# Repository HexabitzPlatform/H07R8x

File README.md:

# H07R8x-Hardware
Hexabitz 10W Stereo Audio Amplifier Module Hardware Design

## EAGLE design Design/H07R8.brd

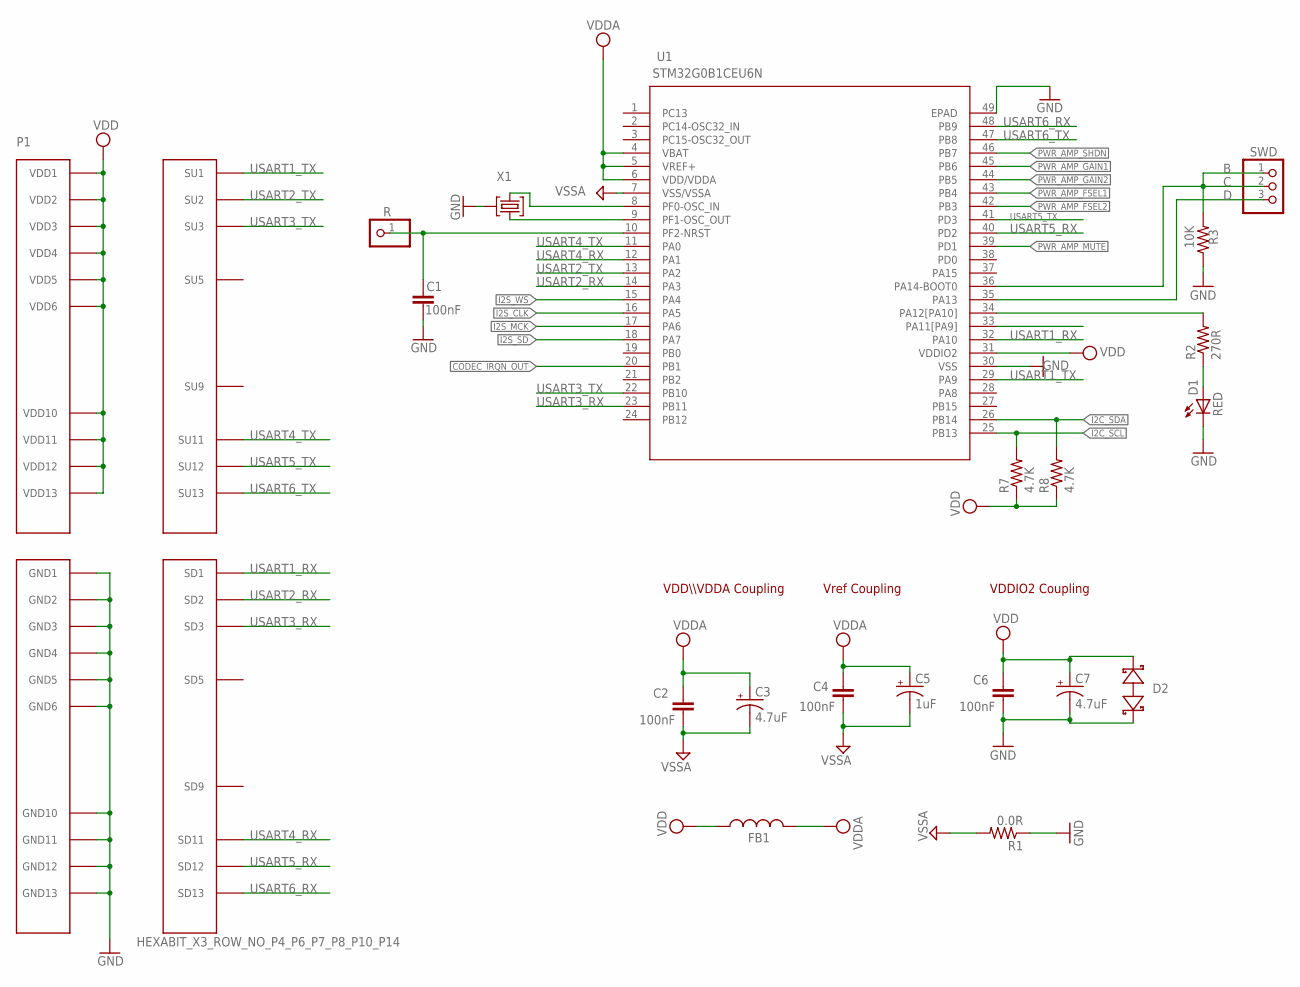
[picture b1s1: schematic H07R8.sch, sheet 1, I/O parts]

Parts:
C1: 100nF; C-0603; TOLERANCE 10%; VOLTAGE_RATING 16.0 V; MPN 0603YC104K4T2A
C2, C4, C6: 100nF; C-0603; TOLERANCE 10%; VOLTAGE_RATING 16.0 V; MPN '0603YC104K4T2A
C3: 4.7uF; C-0805-POL; TOLERANCE 20%; VOLTAGE_RATING 10.0 V; MPN '10TPU4R7MSI
C5: 1uF; C-0805-POL; TOLERANCE 20%; VOLTAGE_RATING 10.0 V; MPN 'CC0805KKX7R7BB105
C7: 4.7uF; C-0805-POL; TOLERANCE 10%; VOLTAGE_RATING 16.0 V; MPN '10TPU4R7MSI
D1: RED; VLMS1300-GS08
D2: BOURNS_CDSOD323-T03SCBOURNS_CDSOD323-T03SC_0_0; BOURNS_CDSOD323-T03SC_0
FB1: FB-TDK_MMZ1608Y300B; MPN MMZ1608Y300BTA00
P1: HEXABIT_X3_ROW_NO_P4_P6_P7_P8_P10_P14
R: PINHD-1X1; 1X01
R1: 0.0R; R-0603; MPN RC0603JR-070RL
R2: 270R; R-0603; MPN 'ERJ-3GEYJ271V
R3: 10K; R-0603; MPN '060300J0103T5E
R7, R8: 4.7K; R-0603; TOLERANCE ±1%; MPN RMCF0603FT4K70
SWD: PINHD-1X3; 1X03
TRIMBLE-LOGO3: HEXA-LOGO
U1: STM32G0B1CEU6N; HEXABITZ_ICS_QFN_B1CEU6_STM-L
X1: 8MHZ; XTALL_CSTCE8M00G52; MPN CSTNE8M00G550000R0

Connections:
C: R3.2, SWD.1, SWD.2, U1.36 (PA14-BOOT0)
CODEC_IRQN_OUT: U1.20 (PB1); also elsewhere on the board
D: SWD.3, U1.35 (PA13)
GND: C1.1, C6.1, C7.2 (-), D1.C, D2.1 (A), P1.PAD_PD15 (GND1), P1.PAD_PD16 (GND2), P1.PAD_PD17 (GND3), P1.PAD_PD18 (GND4), P1.PAD_PD19 (GND5), P1.PAD_PD24 (GND6), P1.PAD_PD25 (GND10), P1.PAD_PD26 (GND11), P1.PAD_PD27 (GND12), P1.PAD_PD28 (GND13), R1.1, R3.1, U1.30 (VSS), U1.49 (EPAD), X1.P$2 (2)
GND1: C2.1, C3.2 (-), C4.1, C5.2 (-), R1.2, U1.7 (VSS/VSSA); also elsewhere on the board
I2C_SCL: R7.2, U1.25 (PB13); also elsewhere on the board
I2C_SDA: R8.2, U1.26 (PB14); also elsewhere on the board
I2S_CLK: U1.16 (PA5); also elsewhere on the board
I2S_MCK: U1.17 (PA6); also elsewhere on the board
I2S_SD: U1.18 (PA7); also elsewhere on the board
I2S_WS: U1.15 (PA4); also elsewhere on the board
unnamed: U1.8 (PF0-OSC_IN), X1.P$1 (1)
unnamed: U1.9 (PF1-OSC_OUT), X1.P$3 (3)
unnamed: R2.2, U1.34 (PA12[PA10])
unnamed: D1.A, R2.1
unnamed: C1.2, R.1, U1.10 (PF2-NRST)
PWR_AMP_FSEL1: U1.43 (PB4); also elsewhere on the board
PWR_AMP_FSEL2: U1.42 (PB3); also elsewhere on the board
PWR_AMP_GAIN1: U1.45 (PB6); also elsewhere on the board
PWR_AMP_GAIN2: U1.44 (PB5); also elsewhere on the board
PWR_AMP_MUTE: U1.39 (PD1); also elsewhere on the board
PWR_AMP_SHDN: U1.46 (PB7); also elsewhere on the board
USART1_RX: P1.PAD_PD1 (SD1), U1.32 (PA10)
USART1_TX: P1.PAD_PU1 (SU1), U1.29 (PA9)
USART2_RX: P1.PAD_PD2 (SD2), U1.14 (PA3)
USART2_TX: P1.PAD_PU2 (SU2), U1.13 (PA2)
USART3_RX: P1.PAD_PD3 (SD3), U1.23 (PB11)
USART3_TX: P1.PAD_PU3 (SU3), U1.22 (PB10)
USART4_RX: P1.PAD_PD11 (SD11), U1.12 (PA1)
USART4_TX: P1.PAD_PU11 (SU11), U1.11 (PA0)
USART5_RX: P1.PAD_PD12 (SD12), U1.40 (PD2)
USART5_TX: P1.PAD_PU12 (SU12), U1.41 (PD3)
USART6_RX: P1.PAD_PD13 (SD13), U1.48 (PB9)
USART6_TX: P1.PAD_PU13 (SU13), U1.47 (PB8)
VDD: C6.2, C7.1 (+), D2.2 (C), FB1.1, P1.PAD_PU15 (VDD1), P1.PAD_PU16 (VDD2), P1.PAD_PU17 (VDD3), P1.PAD_PU18 (VDD4), P1.PAD_PU19 (VDD5), P1.PAD_PU24 (VDD6), P1.PAD_PU25 (VDD10), P1.PAD_PU26 (VDD11), P1.PAD_PU27 (VDD12), P1.PAD_PU28 (VDD13), R7.1, R8.1, U1.31 (VDDIO2); also elsewhere on the board
VDDA: C2.2, C3.1 (+), C4.2, C5.1 (+), FB1.2, U1.4 (VBAT), U1.5 (VREF+), U1.6 (VDD/VDDA)

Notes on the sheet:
VDDIO2 Coupling
VDD\\\VDDA Coupling
Vref Coupling

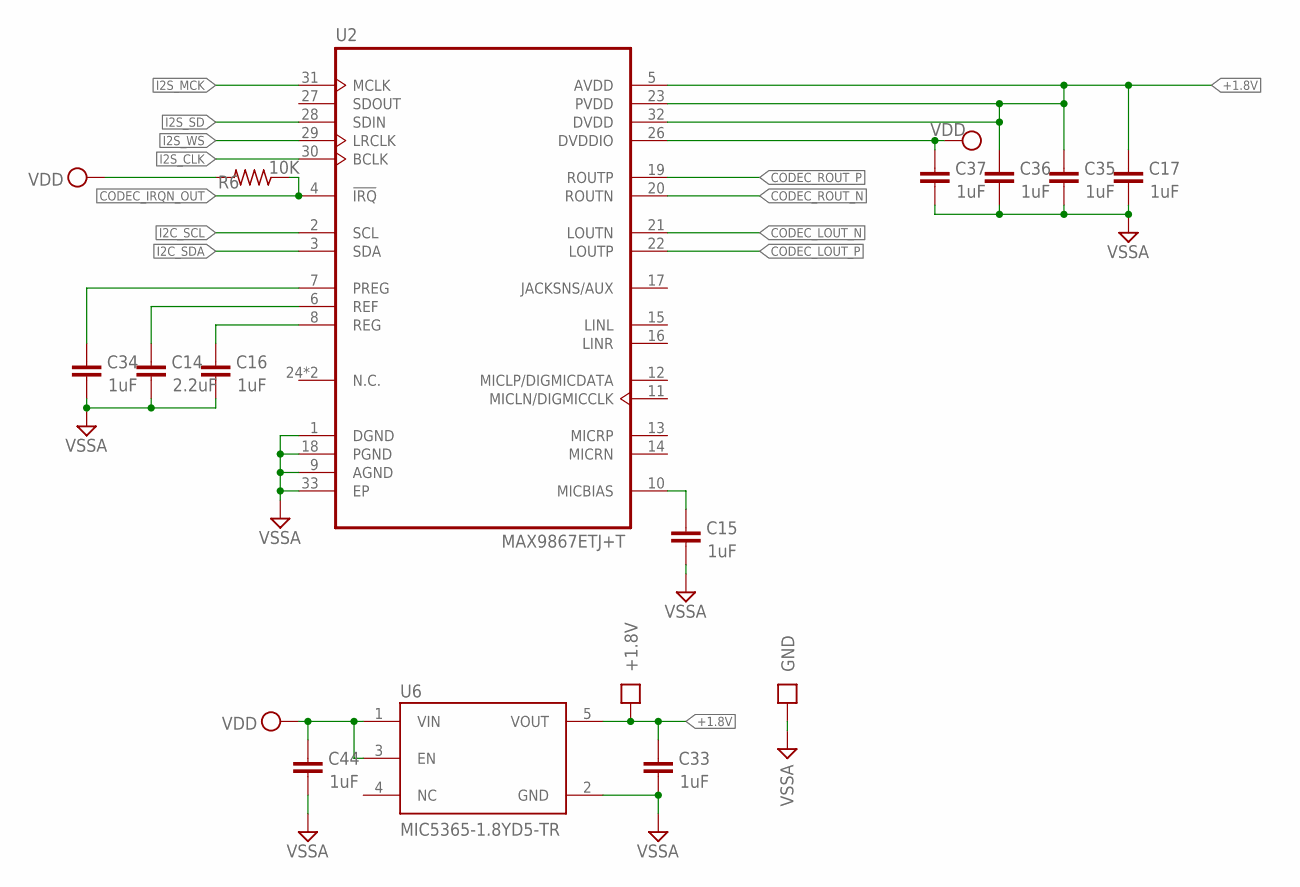
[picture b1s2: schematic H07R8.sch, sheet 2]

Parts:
+1.8V: PAD4
C14: 2.2uF; C-0603; TOLERANCE 10%; VOLTAGE_RATING 16V; MPN CL10A225KO8NNNC
C15, C16, C17, C33, C34, C35, C36, C37, C44: 1uF; C-0603; TOLERANCE 10%; VOLTAGE_RATING 50V; MPN UMK107BJ105KA-T
GND: PAD4
R6: 10K; R-0603; MPN '060300J0103T5E
U2: MAX9867ETJ+T; QFN50P500X500X80-33N
U6: MIC5365-1.8YD5-TRMICROCHIP_MIC5365-1_8YD5-TR_0_0; MICROCHIP_MIC5365-1_8YD5-TR_0

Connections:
+1.8V: +1.8V.P$1, C17.2, C33.2, C35.2, C36.2, U2.5 (AVDD), U2.23 (PVDD), U2.32 (DVDD), U6.5 (VOUT)
CODEC_IRQN_OUT: R6.1, U2.4 (!IRQ); also elsewhere on the board
CODEC_LOUT_N: U2.21 (LOUTN); also elsewhere on the board
CODEC_LOUT_P: U2.22 (LOUTP); also elsewhere on the board
CODEC_ROUT_N: U2.20 (ROUTN); also elsewhere on the board
CODEC_ROUT_P: U2.19 (ROUTP); also elsewhere on the board
GND1: C14.1, C15.1, C16.1, C17.1, C33.1, C34.1, C35.1, C36.1, C37.1, C44.1, GND.P$1, U2.1 (DGND), U2.9 (AGND), U2.18 (PGND), U2.33 (EP), U6.2 (GND); also elsewhere on the board
I2C_SCL: U2.2 (SCL); also elsewhere on the board
I2C_SDA: U2.3 (SDA); also elsewhere on the board
I2S_CLK: U2.30 (BCLK); also elsewhere on the board
I2S_MCK: U2.31 (MCLK); also elsewhere on the board
I2S_SD: U2.28 (SDIN); also elsewhere on the board
I2S_WS: U2.29 (LRCLK); also elsewhere on the board
unnamed: C16.2, U2.8 (REG)
unnamed: C14.2, U2.6 (REF)
unnamed: C34.2, U2.7 (PREG)
unnamed: C15.2, U2.10 (MICBIAS)
VDD: C37.2, C44.2, R6.2, U2.26 (DVDDIO), U6.1 (VIN), U6.3 (EN); also elsewhere on the board

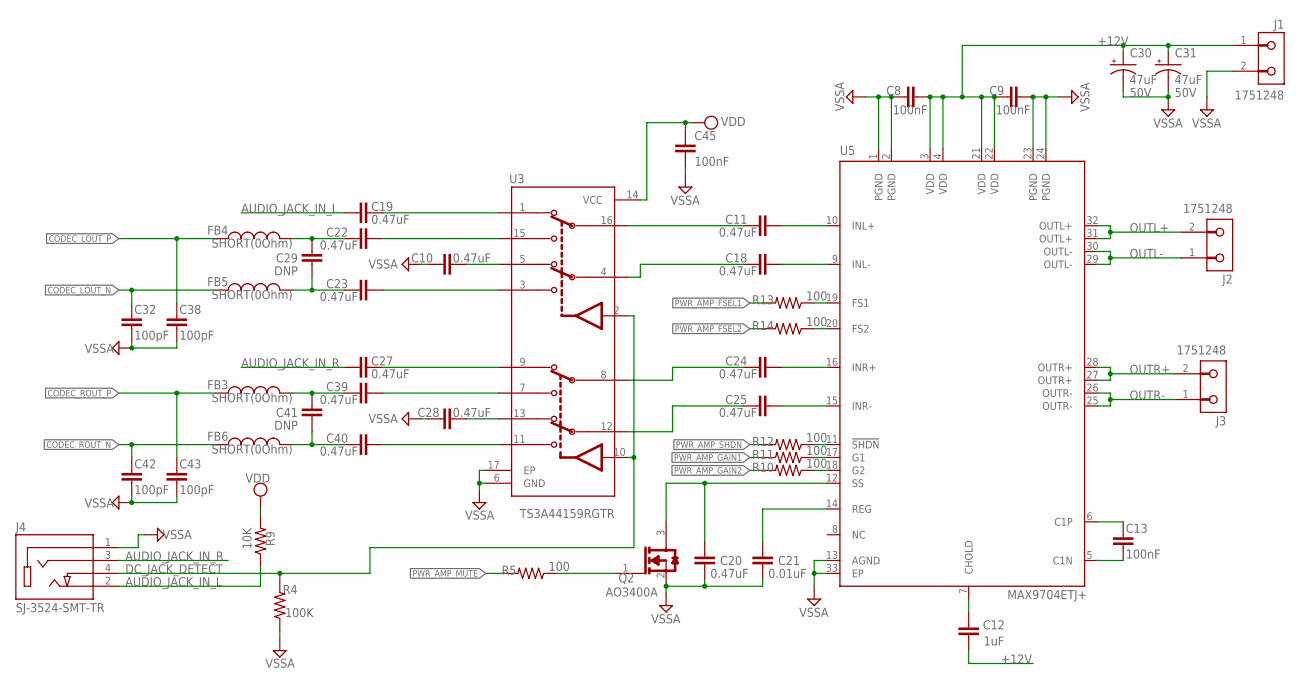
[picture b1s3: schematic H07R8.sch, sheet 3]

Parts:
C8, C9, C13, C45: 100nF; C-0603; TOLERANCE 10%; VOLTAGE_RATING 25.0 V; MPN CL10B104KA8NNNC
C10, C11, C18, C19, C20, C22, C23, C24, C25, C27, C28, C39, C40: 0.47uF; C-0603; TOLERANCE 10%; VOLTAGE_RATING 25.0 V; MPN C1608X5R1E474K080AC
C12: 1uF; C-0603; TOLERANCE 10%; VOLTAGE_RATING 50V; MPN UMK107BJ105KA-T
C21: 0.01uF; C-0603; TOLERANCE 10%; VOLTAGE_RATING 50.0 V; MPN CC0603KRX7R9BB103
C29, C41: DNP; C-0603
C30, C31: 47uF; PANASONIC_D
C32, C38, C42, C43: 100pF; C-0603; TOLERANCE 10%; VOLTAGE_RATING 50.0 V; MPN CC0603KPX7R9BB101
FB3, FB4, FB5, FB6: SHORT(0Ohm); FB-0603; MPN RC0603FR-070RL
J1, J2, J3: 1751248PHOENIX_CONTACT_1751248_0_0; PHOENIX_CONTACT_1751248_0
J4: SJ-3524-SMT-TR; CUI_SJ-3524-SMT
Q2: AO3400AALPHA_&_OMEGA_SEMICONDUCTOR_AO3400A_0_0; ALPHA_&_OMEGA_SEMICONDUCTOR_AO3400A_0
R4: 100K; R-0603; MPN RC0603FR-10100KL
R5, R10, R11, R12, R13, R14: 100; R-0603; MPN RMCF0603FT100R
R9: 10K; R-0603; MPN '060300J0103T5E
U3: TS3A44159RGTRTEXAS_INSTRUMENTS_TS3A44159RGTR_0_0; TEXAS_INSTRUMENTS_TS3A44159RGTR_0
U5: MAX9704ETJ+; QFN65P700X700X80-33N

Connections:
+12V: C8.1, C9.2, C12.1, C30.+, C31.+, J1.1, U5.3 (VDD), U5.4 (VDD), U5.21 (VDD), U5.22 (VDD)
AUDIO_JACK_IN_L: C19.1, J4.2, R9.1
AUDIO_JACK_IN_R: C27.1, J4.3
CODEC_LOUT_N: C32.2, FB5.1; also elsewhere on the board
CODEC_LOUT_P: C38.2, FB4.1; also elsewhere on the board
CODEC_ROUT_N: C42.2, FB6.1; also elsewhere on the board
CODEC_ROUT_P: C43.2, FB3.1; also elsewhere on the board
DC_JACK_DETECT: J4.4, R4.2, U3.2 (IN1-2), U3.10 (IN3-4)
GND1: C8.2, C9.1, C10.1, C20.2, C21.2, C28.1, C30.-, C31.-, C32.1, C38.1, C42.1, C43.1, C45.2, J1.2, J4.1, Q2.2 (S), R4.1, U3.6 (GND), U3.17 (EP), U5.1 (PGND), U5.2 (PGND), U5.13 (AGND), U5.23 (PGND), U5.24 (PGND), U5.33 (EP); also elsewhere on the board
unnamed: C40.1, C41.1, FB6.2
unnamed: C21.1, U5.14 (REG)
unnamed: C12.2, U5.7 (CHOLD)
unnamed: C22.2, U3.15 (NO1)
unnamed: C23.2, U3.3 (NO2)
unnamed: C13.1, U5.6 (C1P)
unnamed: C39.2, U3.7 (NO3)
unnamed: C40.2, U3.11 (NO4)
unnamed: C19.2, U3.1 (NC1)
unnamed: C13.2, U5.5 (C1N)
unnamed: C27.2, U3.9 (NC3)
unnamed: C22.1, C29.2, FB4.2
unnamed: C23.1, C29.1, FB5.2
unnamed: C39.1, C41.2, FB3.2
unnamed: C10.2, U3.5 (NC2)
unnamed: C28.2, U3.13 (NC4)
unnamed: C11.2, U5.10 (INL+)
unnamed: C11.1, U3.16 (COM1)
unnamed: C18.1, U3.4 (COM2)
unnamed: C24.1, U3.8 (COM3)
unnamed: C25.1, U3.12 (COM4)
unnamed: C18.2, U5.9 (INL-)
unnamed: C24.2, U5.16 (INR+)
unnamed: C20.1, Q2.3 (D), U5.12 (SS)
unnamed: C25.2, U5.15 (INR-)
unnamed: R13.1, U5.19 (FS1)
unnamed: R14.1, U5.20 (FS2)
unnamed: R12.1, U5.11 (!SHDN!)
unnamed: R11.1, U5.17 (G1)
unnamed: R10.1, U5.18 (G2)
unnamed: Q2.1 (G), R5.1
OUTL+: J2.2, U5.31 (OUTL+), U5.32 (OUTL+)
OUTL-: J2.1, U5.29 (OUTL-), U5.30 (OUTL-)
OUTR+: J3.2, U5.27 (OUTR+), U5.28 (OUTR+)
OUTR-: J3.1, U5.25 (OUTR-), U5.26 (OUTR-)
PWR_AMP_FSEL1: R13.2; also elsewhere on the board
PWR_AMP_FSEL2: R14.2; also elsewhere on the board
PWR_AMP_GAIN1: R11.2; also elsewhere on the board
PWR_AMP_GAIN2: R10.2; also elsewhere on the board
PWR_AMP_MUTE: R5.2; also elsewhere on the board
PWR_AMP_SHDN: R12.2; also elsewhere on the board
VDD: C45.1, R9.2, U3.14 (VCC); also elsewhere on the board

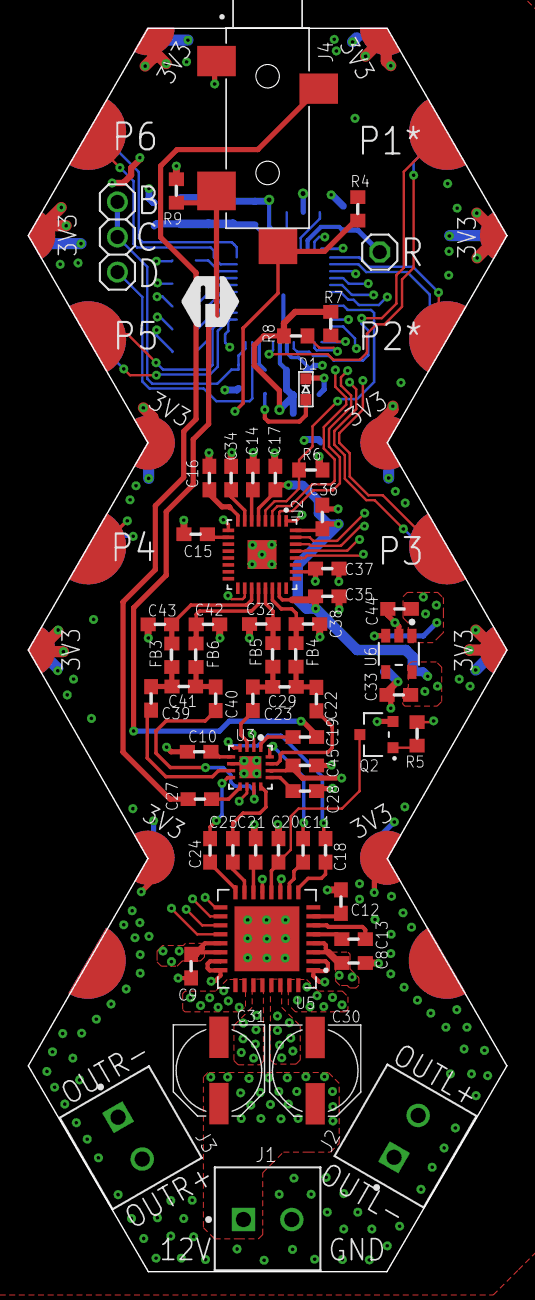
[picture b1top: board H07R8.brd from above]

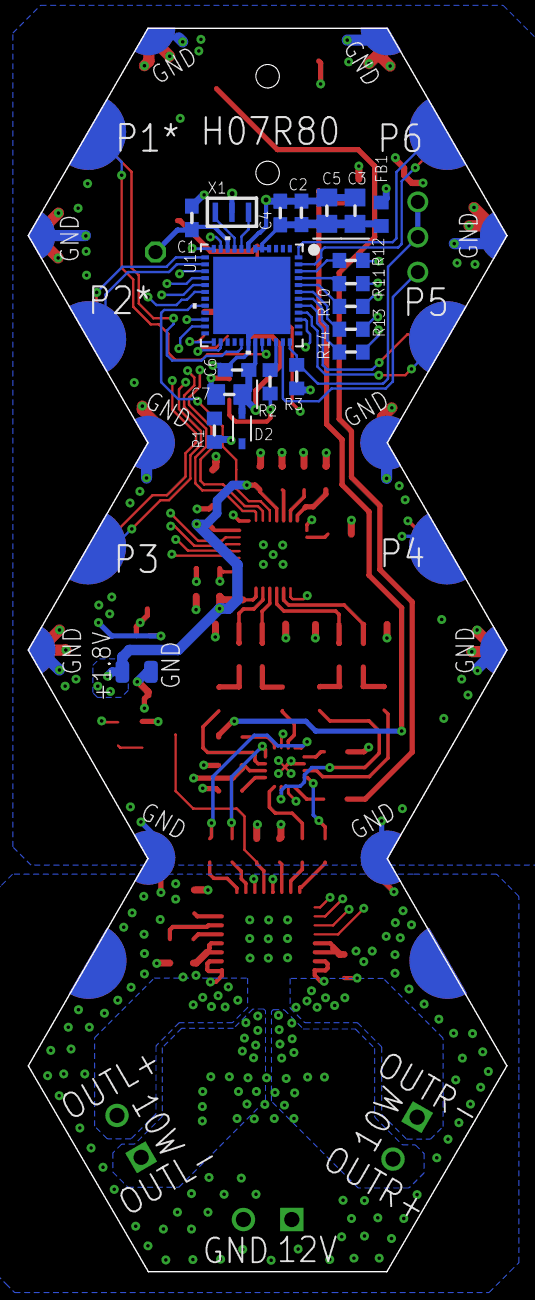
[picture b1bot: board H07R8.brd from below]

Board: 4 copper layers, 34.6 x 90.0 mm, 82 parts (21 on the bottom side), 84 nets.

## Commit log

2023-12-24 -Adding the template files
2024-01-01 Creat H07R80 folder
2024-02-20 - The reviewed version is complete.
2024-02-20 Deleting unnecessary files
2024-04-12 Add TVS diode Edit the logo
2024-04-30 -Update BOM

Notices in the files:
parts and their libraries:
HEXABITZ_ICs: COPYRIGHT: Copyright (C) 2022 Ultra Librarian. All rights reserved.
